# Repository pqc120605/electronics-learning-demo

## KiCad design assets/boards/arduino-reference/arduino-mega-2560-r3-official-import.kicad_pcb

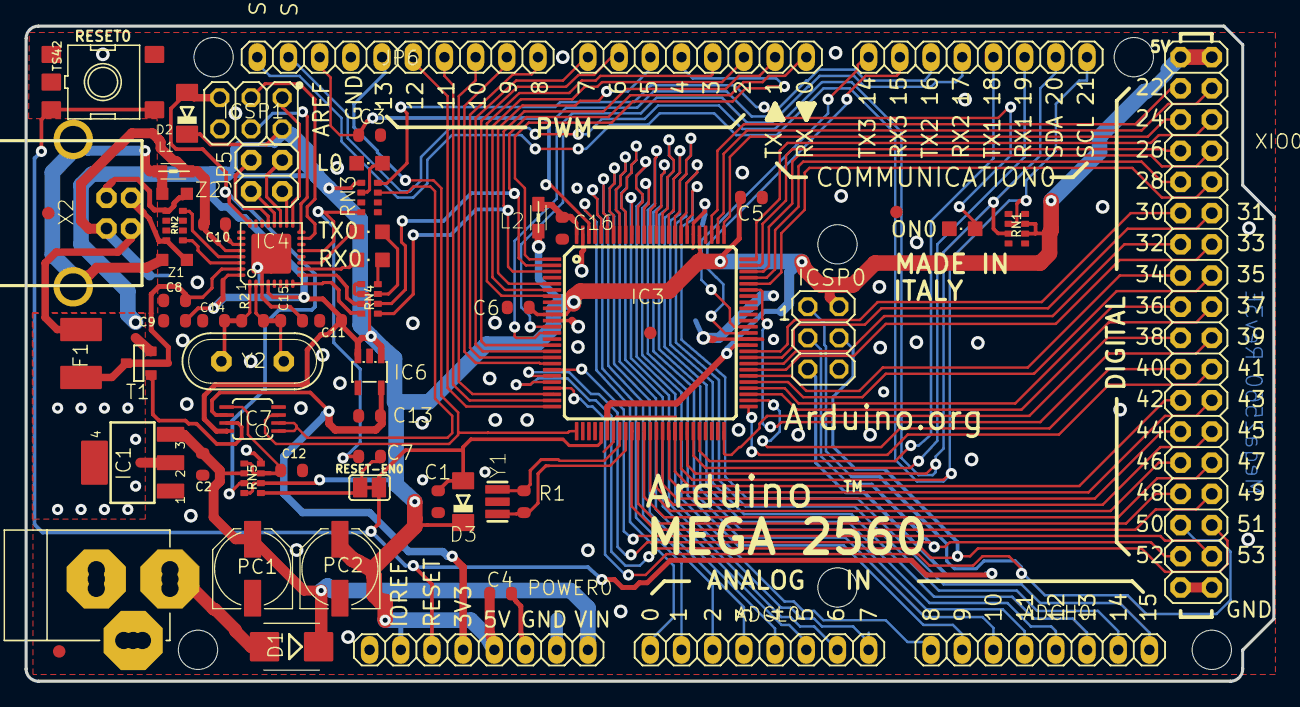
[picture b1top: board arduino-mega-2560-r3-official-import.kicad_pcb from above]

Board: 2 copper layers, 101.6 x 53.3 mm, 72 parts (1 on the bottom side), 111 nets.

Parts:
ADCH0: FH254-108DF08500V; 1X08
ADCL0: FH254-108DF08500V; 1X08
C1, C14, C15: 22p; C0603-ROUND
C2, C3, C4, C5, C6, C7, C8, C9, C11, C12, C16: 100nF; C0603-ROUND
C10, C13: 1uF; C0603-ROUND
COMMUNICATION0: FH254-108DF08500V; 1X08
D1: M7; SMB
D2, D3: CD1206-S01575; MINIMELF
F1: MF-MSMF050-2 500mA; L1812
FD1, FD2, FD3, FD4: FIDUCIALMOUNT; FIDUCIA-MOUNT
GROUND0: SJ
IC1: 1870_LD1117S50CTR; LINEAR_SOT223
IC3: ATMEGA2560-15AU; TQFP100
IC4: ATMEGA16U2-MU; MLF32
IC6: LP2985-33DBVR; SOT23-DBV
IC7: LMV358IDGKR; MSOP08
ICSP0, ICSP1: ICSP; 2X03
JP5: 2x2M - NM; 2X02
JP6: FH254-110DF08500V; 1X10
L0: Yellow; CHIPLED_0805
L1: MH2029-300Y; 0805
L2: 10uH; 0805
ON0: Green; CHIPLED_0805
PC1, PC2: 47uF; PANASONIC_D
POWER0: FH254-108DF08500V; 1X08
PWML0: FH254-108DF08500V; 1X08
R1, R2: 1M; R0603-ROUND
RESET0: TS42
RESET-EN0: SJ
RN1, RN5: 10k; CAY16
RN2: 22R; CAY16
RN3, RN4: 1K; CAY16
RX0: Yellow; CHIPLED_0805
T1: PMV48XP; SOT-23
TX0: Yellow; CHIPLED_0805
U$1, U$2: DNP; FRAME
UNK_HOLE_0: dummyfp0
UNK_HOLE_1: dummyfp1
UNK_HOLE_2: dummyfp2
UNK_HOLE_3: dummyfp3
UNK_HOLE_4: dummyfp4
UNK_HOLE_5: dummyfp5
X1: POWERSUPPLY_DC21MMX; POWERSUPPLY_DC-21MM
X2: PN61729
XIO0: 18x2F-H8.5; 2X18
Y1: CSTCE16M0V53-R0; RESONATOR
Y2: 16MHz; QS
Z1, Z2: BRNCG0603MLC-05E; CT_CN0603

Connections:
8PB4: IC4.18, JP5.1
8PB5: IC4.19, JP5.3
8PB6: IC4.20, JP5.2
8PB7: IC4.21, JP5.4
+3V3: C13.2, IC6.5, IC7.6, POWER0.4
+5V: C4.1, C5.1, C6.1, C9.1, C11.2, D2.C, D3.C, IC1.2, IC1.4, IC3.10, IC3.31, IC3.61, IC3.80, IC4.4, IC4.32, IC6.1, IC6.3, IC7.8, ICSP0.2, ICSP1.2, L2.2, PC2.+, POWER0.2, POWER0.5, RN1.6, RN1.7, RN3.1, RN4.5, RN4.6, RN5.2, RN5.8, T1.2, XIO0.1, XIO0.2
ADC0: ADCL0.1, IC3.97
ADC1: ADCL0.2, IC3.96
ADC2: ADCL0.3, IC3.95
ADC3: ADCL0.4, IC3.94
ADC4: ADCL0.5, IC3.93
ADC5: ADCL0.6, IC3.92
ADC6: ADCL0.7, IC3.91
ADC7: ADCL0.8, IC3.90
ADC8: ADCH0.1, IC3.89
ADC9: ADCH0.2, IC3.88
ADC10: ADCH0.3, IC3.87
ADC11: ADCH0.4, IC3.86
ADC12: ADCH0.5, IC3.85
ADC13: ADCH0.6, IC3.84
ADC14: ADCH0.7, IC3.83
ADC15: ADCH0.8, IC3.82
AREF: C3.1, IC3.98, JP6.3
AVCC: C16.1, IC3.100, L2.1
CMP: C12.2, IC7.5, RN5.3, RN5.5
D+: RN2.5, X2.3, Z2.2
D-: RN2.8, X2.2, Z1.2
DTR: C7.1, IC4.13, RN3.4
GATE_CMD: IC7.7, T1.3
GND: C1.2, C2.2, C3.2, C4.2, C5.2, C6.2, C8.2, C9.2, C11.1, C12.1, C13.1, C14.2, C15.2, C16.2, GROUND0.2, IC1.1, IC3.11, IC3.32, IC3.62, IC3.81, IC3.99, IC4.3, IC4.33, IC6.2, IC7.4, ICSP0.6, ICSP1.6, JP6.4, L0.C, ON0.C, PC1.-, PC2.-, POWER0.6, POWER0.7, RESET0.1, RESET0.2, RN3.5, RN5.4, X1.1, X1.3, XIO0.35, XIO0.36, Y1.2
L13: IC7.1, IC7.2, RN3.7
M8RXD: IC4.9, RN4.7
M8TXD: IC4.8, RN4.8
MISO2: IC4.17, ICSP1.1
MOSI2: IC4.16, ICSP1.4
unnamed: L0.A, RN3.2
unnamed: ON0.A, RN3.8
unnamed: RN4.4, RX0.A
unnamed: RN4.3, TX0.A
PA0: IC3.78, XIO0.3
PA1: IC3.77, XIO0.4
PA2: IC3.76, XIO0.5
PA3: IC3.75, XIO0.6
PA4: IC3.74, XIO0.7
PA5: IC3.73, XIO0.8
PA6: IC3.72, XIO0.9
PA7: IC3.71, XIO0.10
PB0: IC3.19, XIO0.34
PB1: IC3.20, ICSP0.3, XIO0.33
PB2: IC3.21, ICSP0.4, XIO0.32
PB3: IC3.22, ICSP0.1, XIO0.31
PB4: IC3.23, JP6.8
PB5: IC3.24, JP6.7
PB6: IC3.25, JP6.6
PB7: IC3.26, IC7.3, JP6.5
PC0: IC3.53, XIO0.18
PC1: IC3.54, XIO0.17
PC2: IC3.55, XIO0.16
PC3: IC3.56, XIO0.15
PC4: IC3.57, XIO0.14
PC5: IC3.58, XIO0.13
PC6: IC3.59, XIO0.12
PC7: IC3.60, XIO0.11
PD7: IC3.50, XIO0.19
PE0: IC3.2, PWML0.1, RN4.2
PE1: IC3.3, PWML0.2, RN4.1
PE3: IC3.5, PWML0.6
PE4: IC3.6, PWML0.3
PE5: IC3.7, PWML0.4
PG0: IC3.51, XIO0.22
PG1: IC3.52, XIO0.21
PG2: IC3.70, XIO0.20
PG5: IC3.1, PWML0.5
PH3: IC3.15, PWML0.7
PH4: IC3.16, PWML0.8
PH5: IC3.17, JP6.10
PH6: IC3.18, JP6.9
PL0: IC3.35, XIO0.30
PL1: IC3.36, XIO0.29
PL2: IC3.37, XIO0.28
PL3: IC3.38, XIO0.27
PL4: IC3.39, XIO0.26
PL5: IC3.40, XIO0.25
PL6: IC3.41, XIO0.24
PL7: IC3.42, XIO0.23
PWRIN: D1.A, X1.2
RD+: IC4.29, RN2.4
RD-: IC4.30, RN2.1
RESET: C1.1, C7.2, D3.A, IC3.30, ICSP0.5, POWER0.3, RESET0.3, RESET0.4, RESET-EN0.1, RESET-EN0.2, RN5.1
RESET2: D2.A, IC4.24, ICSP1.5, RN5.7
RXD1: COMMUNICATION0.3, IC3.45
RXD2: COMMUNICATION0.5, IC3.12
RXD3: COMMUNICATION0.7, IC3.63
RXL: IC4.10, RX0.C
SCK2: IC4.15, ICSP1.3
SCL: COMMUNICATION0.1, IC3.43, JP6.1, RN1.2
SDA: COMMUNICATION0.2, IC3.44, JP6.2, RN1.3
TXD1: COMMUNICATION0.4, IC3.46
TXD2: COMMUNICATION0.6, IC3.13
TXD3: COMMUNICATION0.8, IC3.64
TXL: IC4.11, TX0.C
UGND: C10.2, GROUND0.1, IC4.28, L1.1, X2.4
USBVCC: C8.1, F1.1, IC4.31, T1.1
USHIELD: L1.2, X2.P$1, X2.P$2, Z1.1, Z2.1
VIN: C2.1, D1.C, IC1.3, PC1.+, POWER0.8, RN5.6
VUCAP: C10.1, IC4.27
XT1: C14.1, IC4.1, R2.1, Y2.2
XT2: C15.1, IC4.2, R2.2, Y2.1
XTAL1: IC3.34, R1.1, Y1.3
XTAL2: IC3.33, R1.2, Y1.1
XVCC: F1.2, X2.1

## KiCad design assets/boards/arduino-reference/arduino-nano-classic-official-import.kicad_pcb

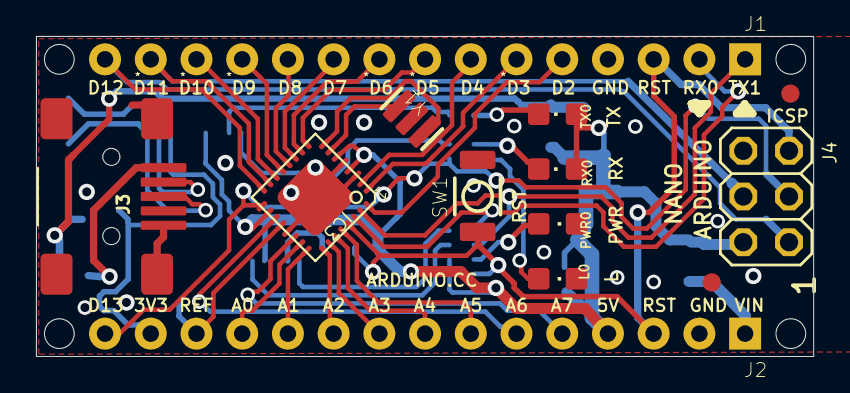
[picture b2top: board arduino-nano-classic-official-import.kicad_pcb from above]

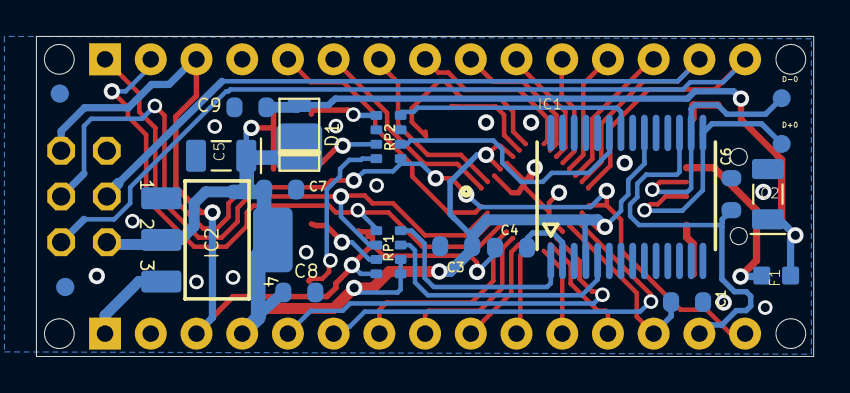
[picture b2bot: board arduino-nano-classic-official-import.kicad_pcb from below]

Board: 2 copper layers, 43.2 x 17.8 mm, 37 parts (17 on the bottom side), 43 nets.

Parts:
C1, C4, C6, C9: 100nF; C0603-ROUND
C2, C5: 4,7uF_16V; TAN-A
C3, C7, C8: 1uF; C0603-ROUND
D1: SS1P3L; DO220AAL
D+0: DNP; TP-1.00MM
D-0: DNP; TP-1.00MM
F1: MFFSMF050; 0603-1608X90N
FRAME1: DNP; FRAME
IC1: FT232RL; SSOP28
IC2: LM1117IMPX-5.0; LINEAR_SOT223
IC3: 328P-MUR; VQFN32
J1, J2: XXXX_STRIPNANO; HEAD15-NOSS
J3: USB-MINI-B_2
J4: 2X03
L0: Yellow; CHIPLED_0805
PWR0: Green; CHIPLED_0805
RP1, RP2: 1K; CAY16
RX0: Red; CHIPLED_0805
SW1: RESET; SMD_157SW
TX0: Green; CHIPLED_0805
U$4, U$5, U$53, U$54: DNP; FD-1-1.5
UNK_HOLE_0: dummyfp0
UNK_HOLE_1: dummyfp1
UNK_HOLE_2: dummyfp2
UNK_HOLE_3: dummyfp3
Y1: 16MHz; RESONATOR

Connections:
3V3: C6.2, IC1.17, J2.14
+5V: C3.1, C5.1, C7.1, C8.1, D1.P$1, IC1.4, IC1.20, IC2.2, IC2.4, IC3.4, IC3.6, IC3.18, J2.4, J4.2, RP1.5, RP1.6, RX0.A, TX0.A
A0: IC3.23, J2.12
A1: IC3.24, J2.11
A2: IC3.25, J2.10
A3: IC3.26, J2.9
A4: IC3.27, J2.8
A5: IC3.28, J2.7
A6: IC3.19, J2.6
A7: IC3.22, J2.5
AREF: C1.1, IC3.20, J2.13
COM: C1.2, C2.2, C3.2, C5.2, C6.1, C7.2, C8.2, C9.2, IC1.7, IC1.18, IC1.21, IC1.25, IC1.26, IC2.1, IC3.3, IC3.5, IC3.21, IC3.33, J1.4, J2.2, J3.1, J3.6, J3.7, J3.8, J3.9, J4.6, L0.C, PWR0.C, RP2.3, RP2.6, SW1.1, Y1.2
D0/RX: IC3.30, J1.2, RP1.1
D1/TX: IC3.31, J1.1, RP1.2
D2: IC3.32, J1.5
D3: IC3.1, J1.6
D4: IC3.2, J1.7
D5: IC3.9, J1.8
D6: IC3.10, J1.9
D7: IC3.11, J1.10
D8: IC3.12, J1.11
D9: IC3.13, J1.12
D10: IC3.14, J1.13
D11/MOSI: IC3.15, J1.14, J4.4
D12/MISO: IC3.16, J1.15, J4.1
D13/SCK: IC3.17, J2.15, J4.3, RP2.1
unnamed: IC3.8, Y1.3
unnamed: IC3.7, Y1.1
unnamed: PWR0.A, RP1.3
unnamed: C4.2, IC1.2
unnamed: D+0.X, IC1.15, J3.3
unnamed: D-0.X, IC1.16, J3.4
unnamed: L0.A, RP2.8
unnamed: IC1.23, RP2.2
unnamed: IC1.22, RP2.4
unnamed: RP2.5, TX0.C
unnamed: F1.2, J3.5
unnamed: RP2.7, RX0.C
RESET: C4.1, IC3.29, J1.3, J2.3, J4.5, RP1.4, SW1.2
RX: IC1.1, RP1.8
TX: IC1.5, RP1.7
VIN: IC2.3, J2.1
VUSB: C2.1, C9.1, D1.P$2, F1.1

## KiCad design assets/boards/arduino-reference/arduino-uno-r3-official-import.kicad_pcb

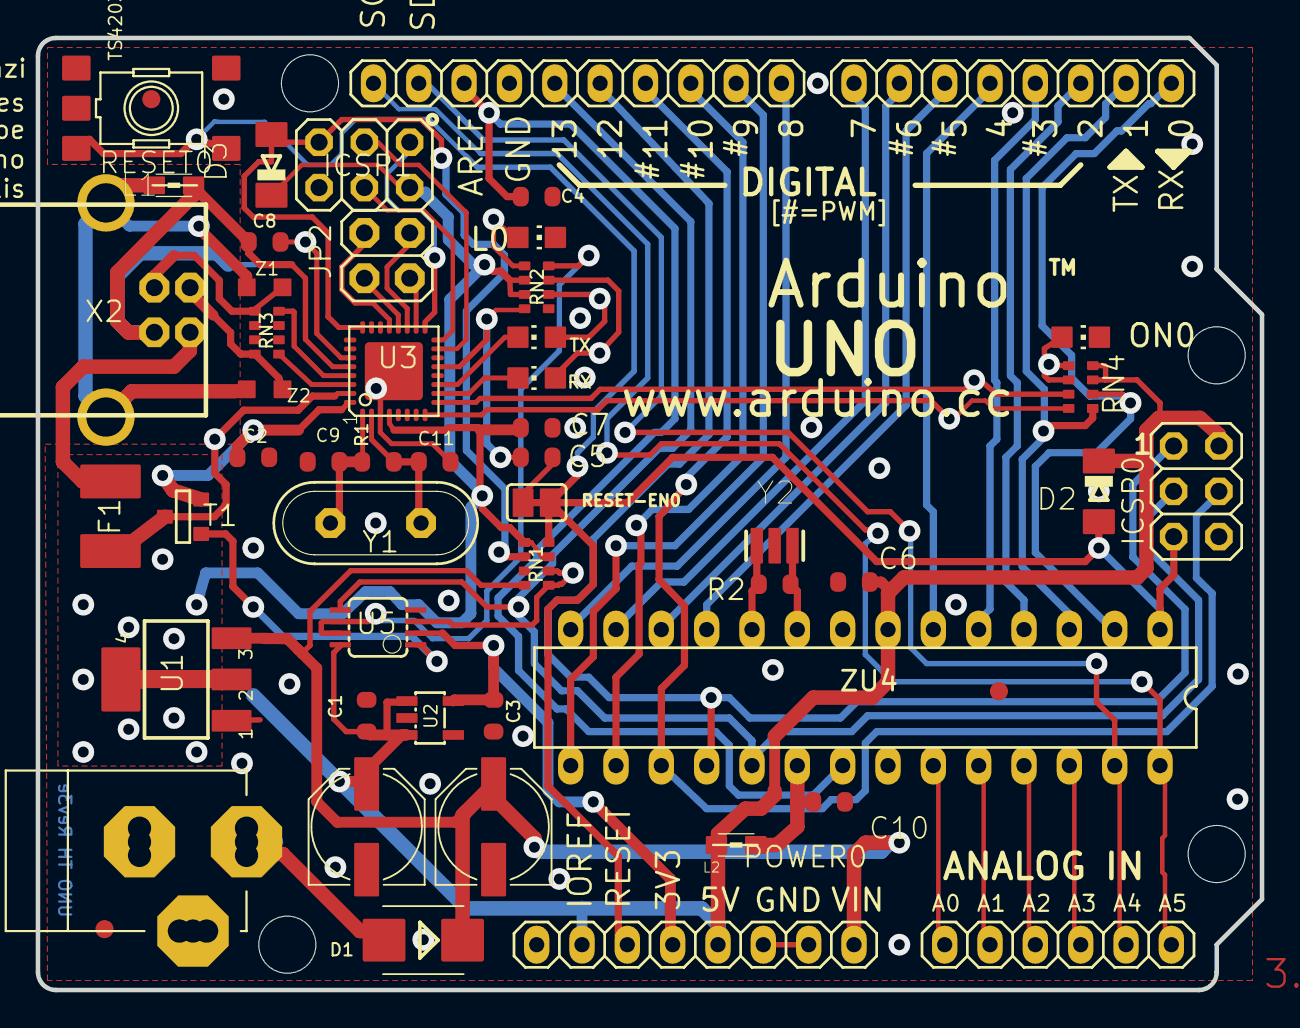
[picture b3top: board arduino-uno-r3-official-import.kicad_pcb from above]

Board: 2 copper layers, 68.6 x 53.3 mm, 120 parts (1 on the bottom side), 61 nets.

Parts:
AD0: 6x1F-H8.5; 1X06
C1, C2, C4, C5, C6, C7, C10: 100n; C0603-ROUND
C3, C8: 1u; C0603-ROUND
C9, C11: 22p; C0603-ROUND
D1: M7; SMB
D2, D3: CD1206-S01575; MINIMELF
F1: MF-MSMF050-2 500mA; L1812
FD1, FD2, FD3: FIDUCIALMOUNT; FIDUCIA-MOUNT
FRAME1: DNP; FRAME
GND_TP0, GND_TP1: TP_SP; TP-SP
GROUND0: SJ
ICSP0, ICSP1: 3x2 M; 2X03
IOH0: 10x1F-H8.5; 1X10
IOL0: 8x1F-H8.5; 1X08
JP2: 2x2 M - NM; 2X02
L0: YELLOW; CHIP-LED0805
L1: BLM21; 0805
L2: 10uH; 0805
ON0: GREEN; CHIP-LED0805
ORIGIN0: TP_SP; TP-SP
PC1, PC2: 47u; PANASONIC_D
POWER0: 8x1F-H8.5; 1X08
R1, R2: 1M; R0603-ROUND
RESET0: TS42031-160R-TR-7260; TS42
RESET-EN0: SJ
RN1: 10K; CAY16
RN2, RN4: 1K; CAY16
RN3: 22R; CAY16
RX0: YELLOW; CHIP-LED0805
T1: FDN340P; SOT-23
TP_0, TP_1, TP_2, TP_3, TP_3V3, TP_4, TP_5, TP_5V0, TP_5V1, TP_6, TP_7, TP_8, TP_9, TP_10, TP_11, TP_12, TP_13: TP_SP; TP-SP
TP_A0, TP_A1, TP_A2, TP_A3, TP_A4, TP_A5: TP_SP; TP-SP
TP_AREF0: TP_SP; TP-SP
TP_CMP0: TP_SP; TP-SP
TP_D+0: TP_SP; TP-SP
TP_D-0: TP_SP; TP-SP
TP_DTR0: TP_SP; TP-SP
TP_GATE0: TP_SP; TP-SP
TP_LCMD0: TP_SP; TP-SP
TP_LL0: TP_SP; TP-SP
TP_MISO2: TP_SP; TP-SP
TP_MOSI2: TP_SP; TP-SP
TP_ONL0: TP_SP; TP-SP
TP_PB4, TP_PB5, TP_PB6, TP_PB7: TP_SP; TP-SP
TP_PWRIN0: TP_SP; TP-SP
TP_RESET0, TP_RESET2: TP_SP; TP-SP
TP_RX0: TP_SP; TP-SP
TP_RXL0: TP_SP; TP-SP
TP_SCK2: TP_SP; TP-SP
TP_SCL0: TP_SP; TP-SP
TP_SDA0: TP_SP; TP-SP
TP_TX0: TP_SP; TP-SP
TP_TXL0: TP_SP; TP-SP
TP_UGND0: TP_SP; TP-SP
TP_USBVCC0: TP_SP; TP-SP
TP_USH0: TP_SP; TP-SP
TP_VIN0: TP_SP; TP-SP
TP_VUCAP0: TP_SP; TP-SP
TP_XT1, TP_XT2, TP_XT3, TP_XT4: TP_SP; TP-SP
TP_XUSB0: TP_SP; TP-SP
TX0: YELLOW; CHIP-LED0805
U1: NCP1117ST50T3G; SOT223
U2: LP2985-33DBVR; SOT23-DBV
U3: ATMEGA16U2-MU(R); MLF32
U5: LMV358IDGKR; MSOP08
UNK_HOLE_0: dummyfp0
UNK_HOLE_1: dummyfp1
UNK_HOLE_2: dummyfp2
UNK_HOLE_3: dummyfp3
X1: POWERSUPPLY_DC21MMX; POWERSUPPLY_DC-21MM
X2: USB-B_TH; PN61729
Y1: 16MHz; QS
Y2: CSTCE16M0V53-R0 16MHZ; RESONATOR
Z1, Z2: CG0603MLC-05E; CT_CN0603
ZU4: ATMEGA328P-PU; DIL28-3

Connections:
+3V3: C3.2, POWER0.4, TP_3V3.X, U2.5, U5.2
+5V: C1.2, C2.2, C6.2, C7.1, D2.C, D3.C, ICSP0.2, ICSP1.2, L2.1, PC2.+, POWER0.2, POWER0.5, RN1.3, RN1.5, RN2.2, RN2.3, RN4.3, RN4.4, T1.2, TP_5V0.X, TP_5V1.X, U1.2, U1.4, U2.1, U2.3, U3.4, U3.32, U5.8, ZU4.7
AD0: AD0.1, TP_A0.X, ZU4.23
AD1: AD0.2, TP_A1.X, ZU4.24
AD2: AD0.3, TP_A2.X, ZU4.25
AD3: AD0.4, TP_A3.X, ZU4.26
AD4/SDA: AD0.5, IOH0.9, TP_A4.X, TP_SDA0.X, ZU4.27
AD5/SCL: AD0.6, IOH0.10, TP_A5.X, TP_SCL0.X, ZU4.28
AREF: C4.2, IOH0.8, TP_AREF0.X, ZU4.21
AVCC: C10.2, L2.2, ZU4.20
CMP: RN1.1, RN1.2, TP_CMP0.X, U5.3
D+: RN3.5, TP_D+0.X, X2.3, Z1.1
D-: RN3.8, TP_D-0.X, X2.2, Z2.1
DTR: C5.1, RN2.4, TP_DTR0.X, U3.13
GATE_CMD: T1.3, TP_GATE0.X, U5.1
GND: C1.1, C2.1, C3.1, C4.1, C6.1, C7.2, C9.2, C10.1, C11.2, GND_TP0.X, GND_TP1.X, GROUND0.1, ICSP0.6, ICSP1.6, IOH0.7, L0.C, ON0.C, PC1.-, PC2.-, POWER0.6, POWER0.7, RESET0.1, RESET0.2, RN1.7, RN2.5, U1.1, U2.2, U3.3, U3.33, U5.4, X1.1, X1.3, Y2.2, ZU4.8, ZU4.22
IO0: IOL0.1, RN4.2, TP_0.X, ZU4.2
IO1: IOL0.2, RN4.1, TP_1.X, ZU4.3
IO2: IOL0.3, TP_2.X, ZU4.4
IO3: IOL0.4, TP_3.X, ZU4.5
IO4: IOL0.5, TP_4.X, ZU4.6
IO5: IOL0.6, TP_5.X, ZU4.11
IO6: IOL0.7, TP_6.X, ZU4.12
IO7: IOL0.8, TP_7.X, ZU4.13
IO8: IOH0.1, TP_8.X, ZU4.14
IO9: IOH0.2, TP_9.X, ZU4.15
L13: RN2.8, TP_LCMD0.X, U5.6, U5.7
M8RXD: RN4.7, TP_RX0.X, U3.9
M8TXD: RN4.8, TP_TX0.X, U3.8
MISO: ICSP0.1, IOH0.5, TP_12.X, ZU4.18
MISO2: ICSP1.1, TP_MISO2.X, U3.17
MOSI: ICSP0.4, IOH0.4, TP_11.X, ZU4.17
MOSI2: ICSP1.4, TP_MOSI2.X, U3.16
unnamed: L0.A, RN2.1, TP_LL0.X
unnamed: ON0.A, RN4.5, RN4.6, TP_ONL0.X
unnamed: RN2.7, RX0.A, TP_RXL0.X
unnamed: RN2.6, TP_TXL0.X, TX0.A
PB4: JP2.1, TP_PB4.X, U3.18
PB5: JP2.3, TP_PB5.X, U3.19
PB6: JP2.2, TP_PB6.X, U3.20
PB7: JP2.4, TP_PB7.X, U3.21
PWRIN: D1.A, TP_PWRIN0.X, X1.2
RD+: RN3.4, U3.29
RD-: RN3.1, U3.30
RESET: C5.2, D2.A, ICSP0.5, POWER0.3, RESET0.3, RESET0.4, RESET-EN0.1, RESET-EN0.2, RN1.4, TP_RESET0.X, ZU4.1
RESET2: D3.A, ICSP1.5, RN1.6, TP_RESET2.X, U3.24
RXLED: RX0.C, U3.10
SCK: ICSP0.3, IOH0.6, TP_13.X, U5.5, ZU4.19
SCK2: ICSP1.3, TP_SCK2.X, U3.15
SS: IOH0.3, TP_10.X, ZU4.16
TP_VUCAP: C8.1, TP_VUCAP0.X, U3.27
TXLED: TX0.C, U3.11
UGND: C8.2, GROUND0.2, L1.1, TP_UGND0.X, U3.28, X2.4
USBVCC: F1.1, T1.1, TP_USBVCC0.X, U3.31
USHIELD: L1.2, TP_USH0.X, X2.P$1, X2.P$2, Z1.2, Z2.2
VIN: D1.C, PC1.+, POWER0.8, RN1.8, TP_VIN0.X, U1.3
XT1: C9.1, R1.1, TP_XT3.X, U3.1, Y1.2
XT2: C11.1, R1.2, TP_XT4.X, U3.2, Y1.1
XTAL1: R2.1, TP_XT1.X, Y2.3, ZU4.9
XTAL2: R2.2, TP_XT2.X, Y2.1, ZU4.10
XUSB: F1.2, TP_XUSB0.X, X2.1
